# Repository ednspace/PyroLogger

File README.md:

For when you the Pyro, needs to log!!!
======================================

Summary
----

A long standing project (since early 2005) to log and provide real time graphing of wood, electric, or gas kiln firings.
This project by necessity requires a hardware and software combination and through the years many have been tried with 
varying degrees of success. Most attempts are preserved here for posterity sake.

The Current Version
-----------
The most recent version of the hardware uses the Teensy 3.1 for the microcontroller, a custom made daughter board that has an SD card and phone jack
 to connect the sensors. The sensors are [MAX31850K from Adafruit](http://www.adafruit.com/products/1727). The GUI is now handled with a customized interface
 for the amazing [MegunoLink](http://www.megunolink.com/).
 While buying modular hardware and using software that requires a modest licensing fee adds to the overall build cost it makes the 
 hardware and software a bit more accessible to the novice experimenter. 
 Hopefully this will enable more people to get at their kiln data and improve their future firings and learn from the ones they have done in the past.

History
-----
If you dig around in the archives you will find early versions of the code that relied on Python, WxPython for a GUI, and provided a front end for a custom piece of hardware. The hardware at that time was based on a microchip PIC microcontroller and addressed a one wire bus and a DS2760A to ultimately digitize two analog type K thermocouples. The combination of hardware and software was used to collect, display and log the temperature. Many variations of the code are here and all of hardware versions of the electronics also. Many early graphs generated with that hardware software combination are in the testing folder. Most of the work was done on the WxGauge and GUI versions. Its not very organized, but feel free to poke around and use what you need.

Enjoy... ED

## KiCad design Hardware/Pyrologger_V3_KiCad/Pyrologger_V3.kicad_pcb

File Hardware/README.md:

Hardware Lives Here
---------

The folder Pyrologger_V3_KiCad contains the latest board files. Its a daughter board for 
the teensy 3.1 that has connections for the thermocouple sensors and an SD card.

The folder ds2760-pcb contains the orginal board files for the pyrometer 
sensor. The chip is a ds2760 lithium ion battery monitor from Maxim now 
Dallas Semiconductor.  It uses the one wire bus to get the mv drop over 
the shunt resistor which in this case is actually a type K 
thermocouple. The files where generated with Linux-PCB and the 
schematics are in gschem.  The LMD file is for driving an LPKF circuit 
board plotter to cut out the board.

The folder 16F88_FT232RL contains the board files and schematic for the 
microcontroller interface to the computer.  It uses a microchip 
technology 16F88 and an FTDI chip to make a serial connection through 
USB.  The microcontroller board is accessed with by the wxPython GUI 
software which collects the data and displays it on screen.  The board 
files where done with Eagle.

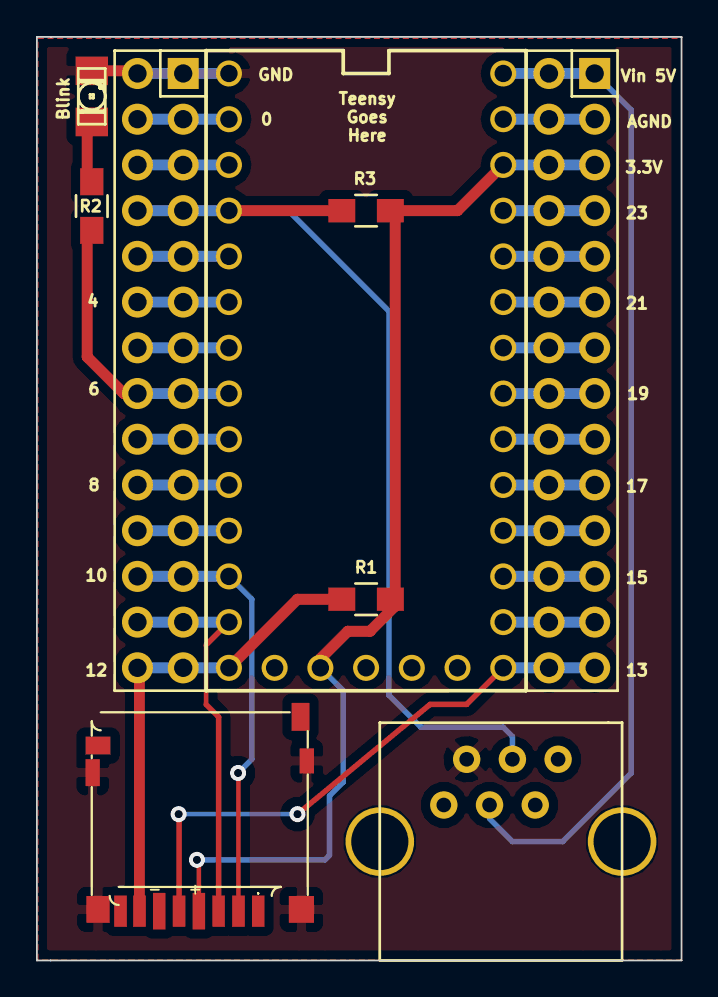
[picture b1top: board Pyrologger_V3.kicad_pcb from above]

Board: 2 copper layers, 35.8 x 51.3 mm, 9 parts (0 on the bottom side), 29 nets.

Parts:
D1: LED; LED-1206
J1: RJ12; RJ12_E
P1, P2: CONN_02X14; Socket_Strip_Straight_2x14
R1: 10K; R_0805_HandSoldering
R2: 330; R_0805_HandSoldering
R3: 4.7K; R_0805_HandSoldering
U1: MICRO-SDCARD_MICRO-SDCARD; DM3D-MicroSD
U2: TEENSY_3.1_BASIC_TEENSY_3.1_BASIC; TEENSY_3.1_BASIC

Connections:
+3.3V: P2.5, P2.6, R1.1, R3.1, U2.3.3V
+5V: J1.3, P2.1, P2.2, U2.VIN
/AGND: P2.3, P2.4, U2.AGND
/DQ: J1.4, P1.7, P1.8, R3.2, U2.2
/MISO: P1.27, P1.28, R1.2, U1.DAT0, U2.12
/MOSI: P1.25, P1.26, U1.CMD, U2.11
/PIN0: P1.3, P1.4, U2.0
/PIN1: P1.5, P1.6, U2.1
/PIN3: P1.9, P1.10, U2.3
/PIN4: P1.11, P1.12, U2.4
/PIN5: P1.13, P1.14, U2.5
/PIN6: P1.15, P1.16, R2.1, U2.6
/PIN7: P1.17, P1.18, U2.7
/PIN8: P1.19, P1.20, U2.8
/PIN9: P1.21, P1.22, U2.9
/PIN14: P2.25, P2.26, U2.14/A
/PIN15: P2.23, P2.24, U2.15/A
/PIN16: P2.21, P2.22, U2.16/A
/PIN17: P2.19, P2.20, U2.17/A
/PIN18: P2.17, P2.18, U2.18/A
/PIN19: P2.15, P2.16, U2.19/A
/PIN20: P2.13, P2.14, U2.20/A
/PIN21: P2.11, P2.12, U2.21/A
/PIN22: P2.9, P2.10, U2.22/A
/PIN23: P2.7, P2.8, U2.23/A
/SCK: P2.27, P2.28, U1.CLK, U2.13
/SS: P1.23, P1.24, U1.CD/D, U2.10
GND: D1.2, J1.2, P1.1, P1.2, U1.GND1, U1.GND2, U1.GND3, U1.GND4, U2.GND
unnamed: D1.1, R2.2

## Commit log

2008-01-17 test change
2008-01-17 Removed the ports file
2008-03-13 This is the first update since switching over to wxpython. Migration went pretty smoothly. Lots more capability without much of a sacrafice. I like it!!!
2008-03-14 This is after a bunch of work with the wx widgets version, changing over to the matplotlib wxbackground api instead of pylab and static images.
2008-03-17 Added buttons fixed multiple subplot problems, doesn't eat up CPU any more!
2008-03-19 Lots of changes
2008-05-18 Got autosave working, added some checkbox menu items for debug and autosave, minor tweaking of the code to make checkbox menu items work, some new graphs etc...
2008-05-30 Just some updated graphs after the woodfire testing.
2008-06-02 After the start of the change to two seperate screens for gauges and graphs. Major code changes after the wood fire experiment of Bridgets country kiln
2008-06-06 Finally got everything into sizers, updated thermometer class, also added a couple of status boxes.
2008-08-05 Few minor tweaks to the pyrologger since the last firing. Plus did a glaze fire which is added.
2008-12-02 Not much changed just updated the old pyrologger file, but failed to get it to work in time for Rogers fireing, maybe next time.
2009-03-23 This is the start of an update, for the WXthermo to log two thermocouples at the same time, for Rogers Fireing
2009-03-27 This is a major rewrite. Mainly for two instead of one thermocouple. Also lots of bug fixes.
2009-04-08 after the firing
2009-04-21 Add the serial port search feature and quit button now works, more code cleanup, installed eclipse and pydev pluggin
2009-04-25 coming in from teh lappy
2009-06-04 Just moved things around again, trying to get organized, wow, what a mess. Somehow I need to gain some discipline.
2010-08-04 No major changes, just adding fire data from Bridgets Kiln Also made a minor change to the graph so it wouldn't keep showing the back thermo which was not present.
2010-11-09 Just an update to get the last firing into the repo!
2011-10-20 Just some house cleaning after moving over to GitHub from GoogleCode. I added some README's got rid of some old files. Added the board files and changed some folder names etc...
2011-10-26 Changed the thermocouple coefficients for the ambient sensors and added a low and high set for the thermocouples. Pretty major overhaul and still testing. Going to know more after this fireing. The p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
2011-10-26 This shot same as the last one... Still learning GIT
2011-11-10 Just pushing out the latest woodfire from October 2011 Over 11,000 points logged during 4 days ;)
2012-04-13 Just removing some old crusty graph data...
2012-09-03 Just getting organized
    Moving files around after getting everything up on the laptop drive
2012-12-21 Just uploading new graphs and changes
2012-12-22 Trying to fix the graphs directory
2014-11-12 Added V2 stuff to repo duckies in a row for another development stab
2014-11-13 More Ogranizing
2014-11-13 adding graphs and fake thermocouple stuff
2014-11-13 Changed notes file in pyrologger new hardware
2014-12-29 adding in the new working teensy software before I start piddling about making changes. This commit works and is pretty solid though not feature rich.
2014-12-31 Added Temperature conversion buttons and a sample rate button to the new interface panel, changes to micro code plus MLP GUI.
2015-02-12 Updating with a new Kicad schematic for the teensy version of the pyrologger. Not complete yet but close
2015-05-14 finished off the kicad board file and starting to work on the arduino code
2015-05-22 Switched to the Visual Micro Atmel code editor, board files updated, general code cleanup and first stab rolling average filter.
2015-05-24 Averaging is now working in code and GUI
2015-06-04 Some enclosure attempts and GUI update with a status update, general code clean up.
2015-06-04 Pushing up Enclosure files and GUI status additions. SD card access at least for logging data is basically working also.
2015-06-04 Updating the stl files for the enclosure gcode may still change but for now matches
2015-06-28 Adding a README and some images plus copy of hex file
2015-06-28 Moving stuff around cleaning up README
2015-06-28 again... with the README
2015-06-28 Added more READMEs and some more Images to front README project cleanup
2015-06-28 Adding more info to the READMEs jeez
2015-06-28 push spelling error push
2015-06-30 Changed link to right board on Adafruit
2016-07-22 adding all the code for the teensy
